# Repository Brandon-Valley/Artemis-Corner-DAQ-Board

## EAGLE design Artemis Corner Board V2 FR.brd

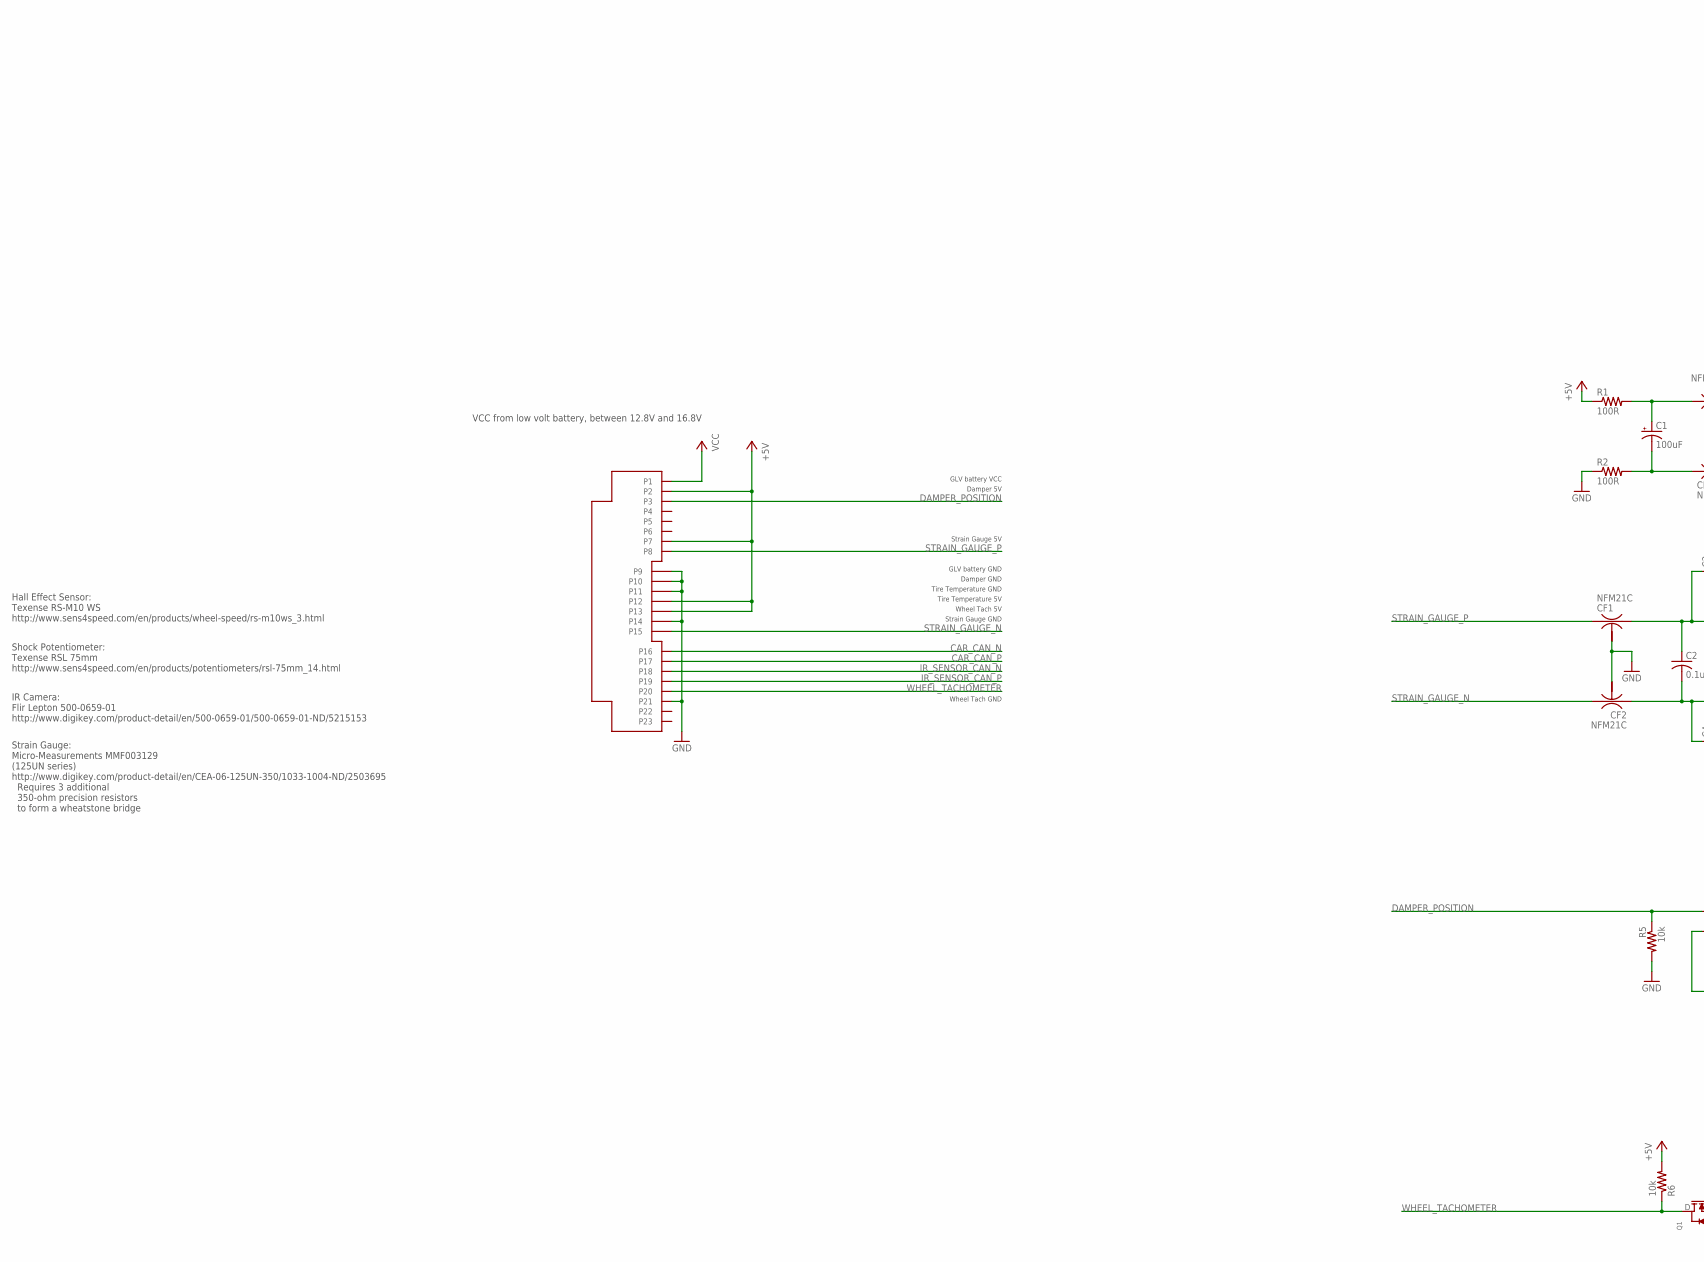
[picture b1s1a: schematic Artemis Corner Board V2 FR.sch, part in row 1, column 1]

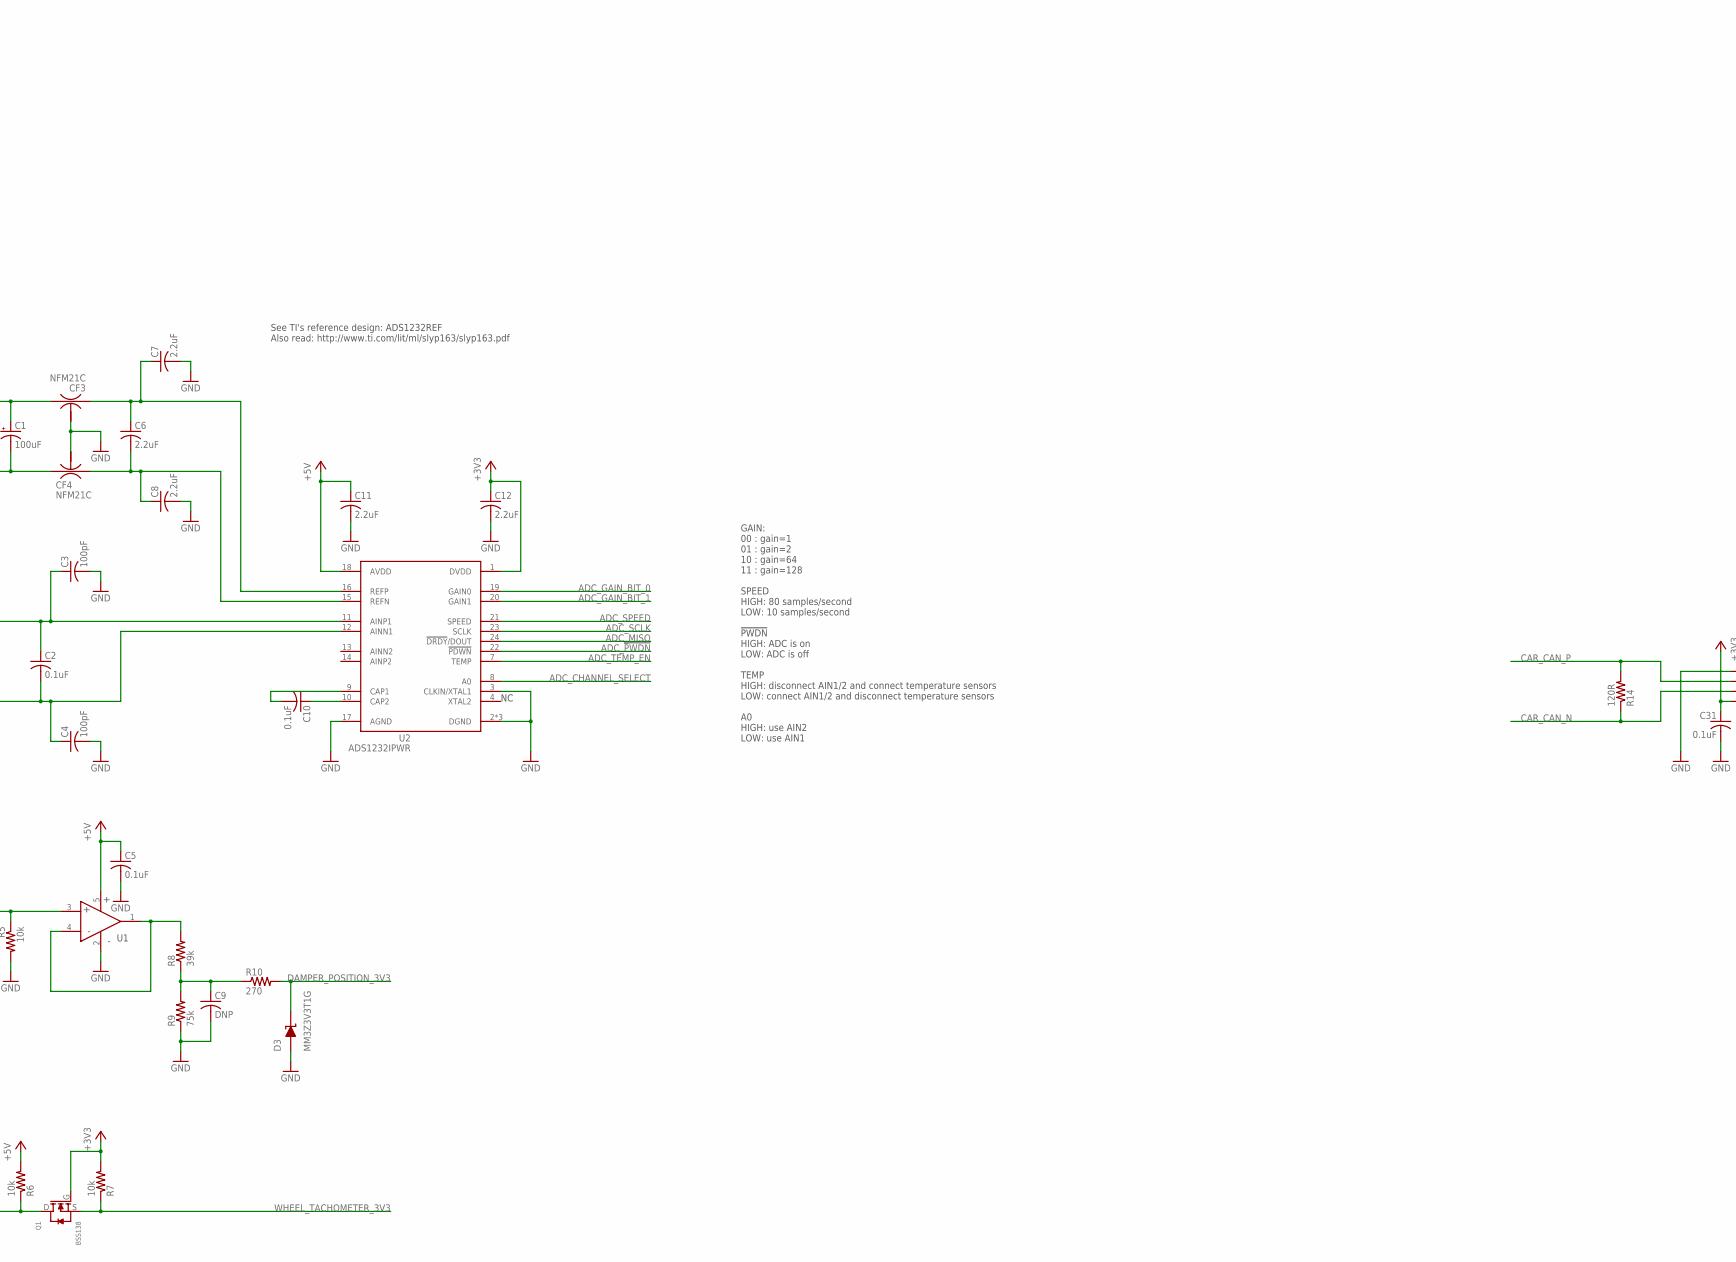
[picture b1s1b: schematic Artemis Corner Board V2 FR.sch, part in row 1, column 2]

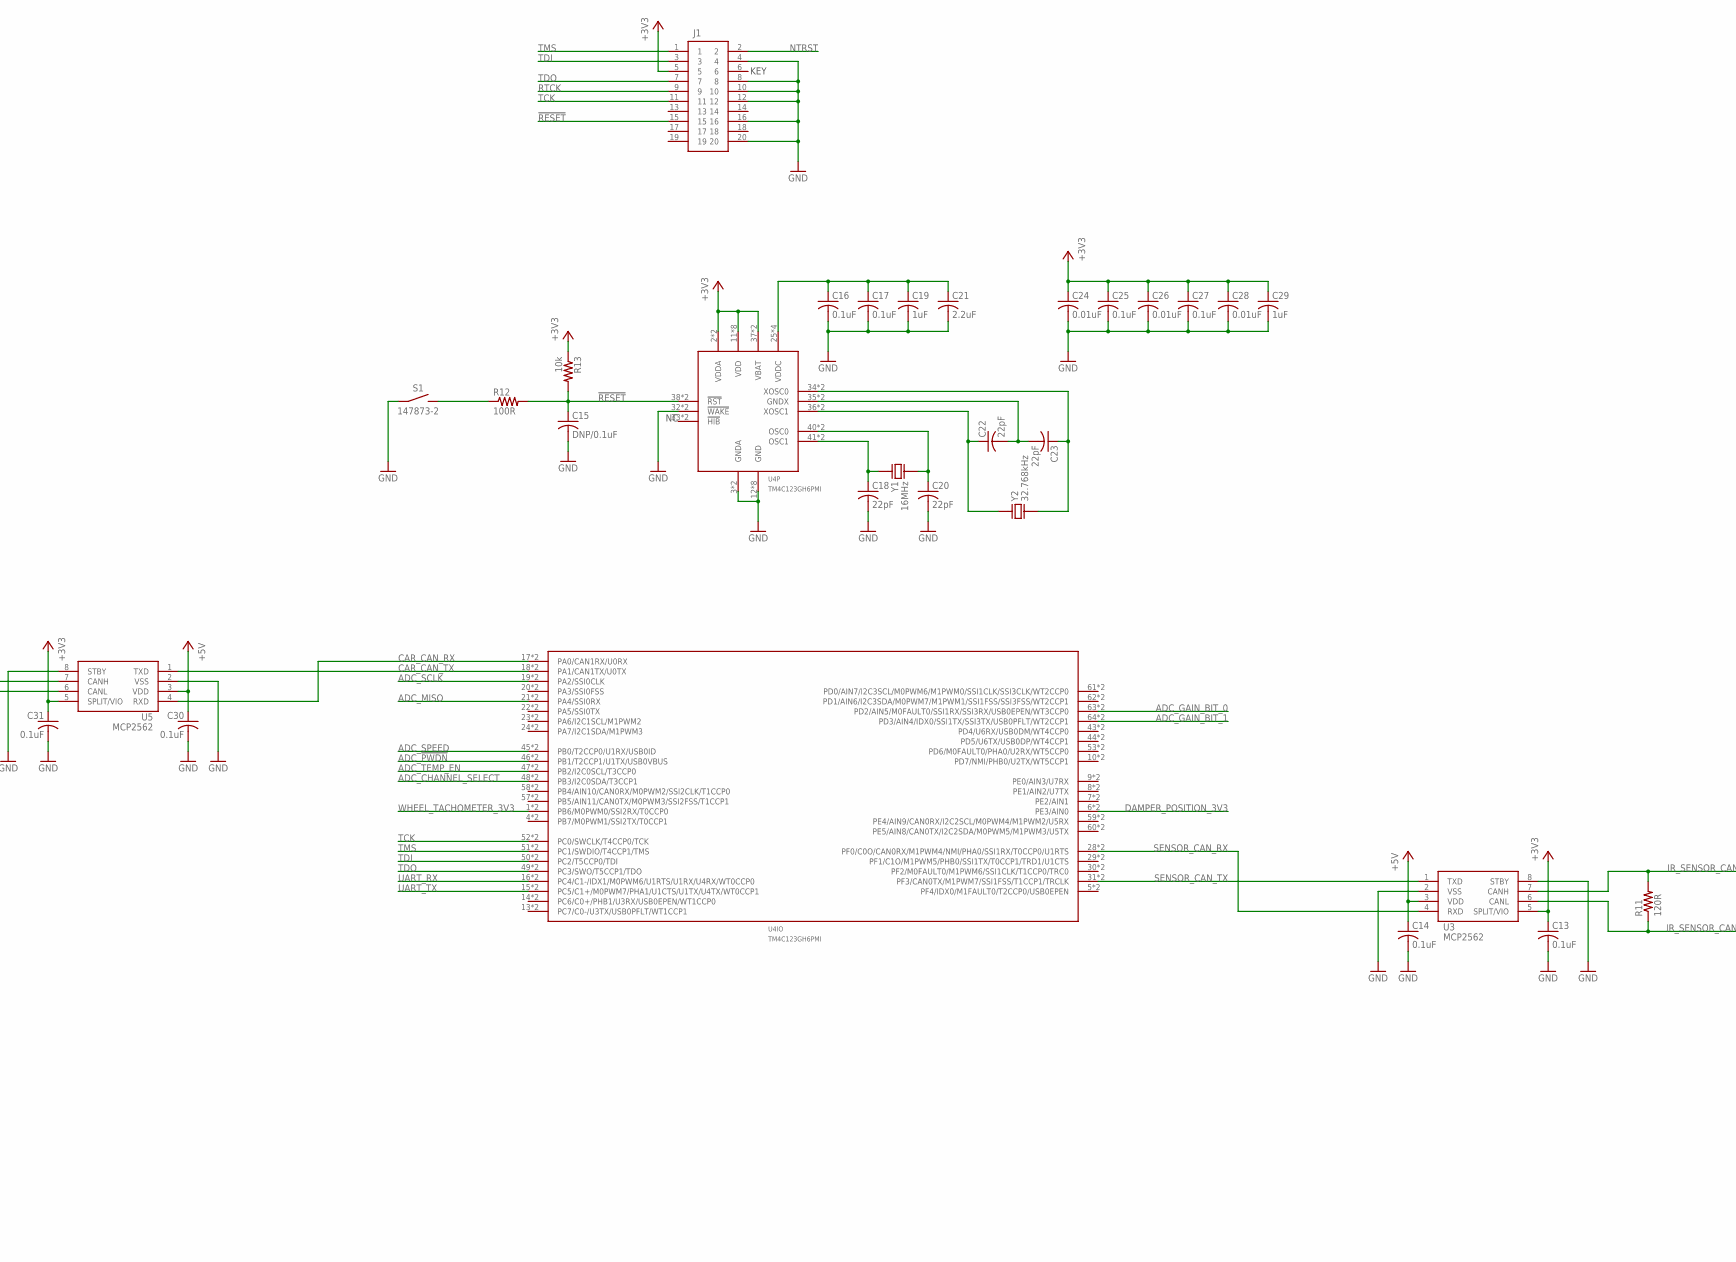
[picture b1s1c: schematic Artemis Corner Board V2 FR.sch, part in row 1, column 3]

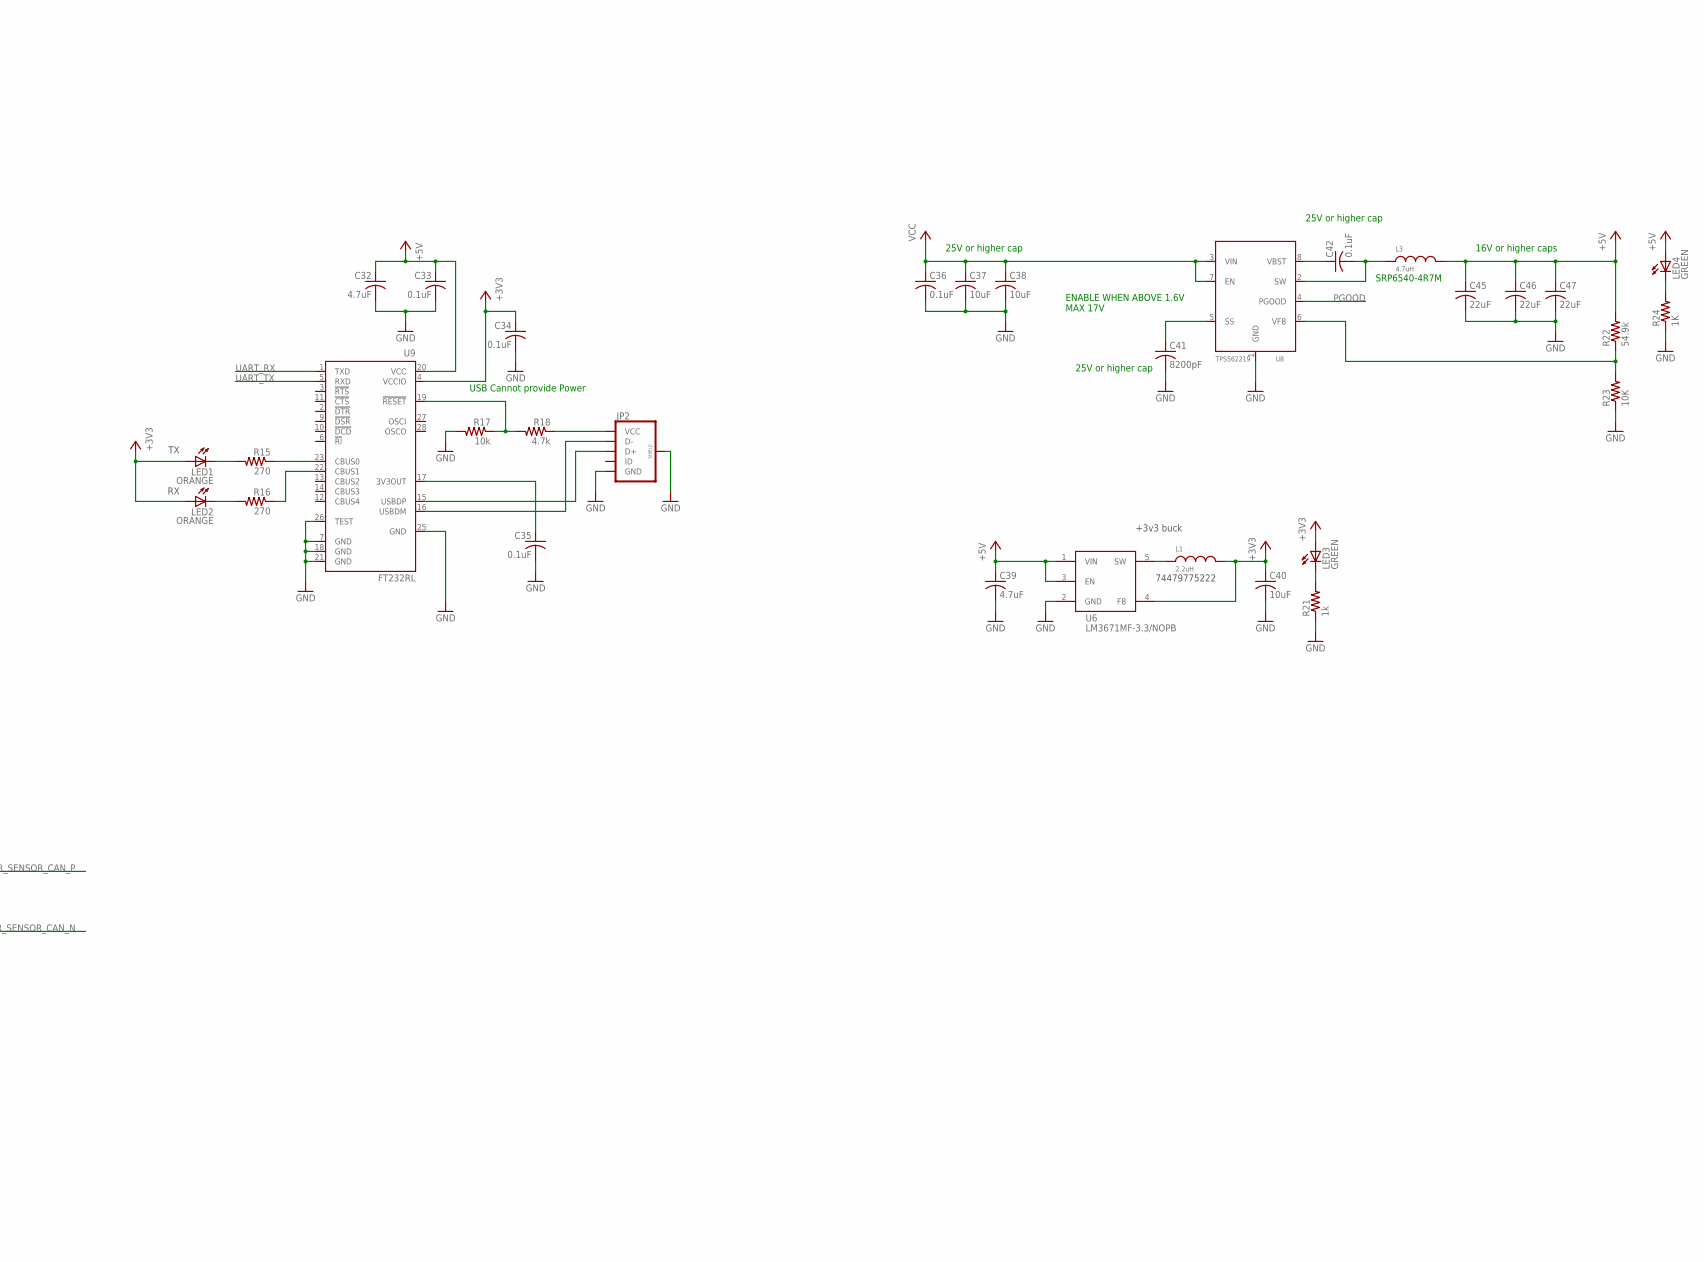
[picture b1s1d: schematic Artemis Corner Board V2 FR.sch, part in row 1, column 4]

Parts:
C1: 100uF; D/7343-31W; PARTNO T494D107K010AT
C2, C10: 0.1uF; C0805; PARTNO *
C3, C4: 100pF; C0805; PARTNO *
C5, C13, C14, C16, C17, C25, C27, C30, C31, C33, C34, C35, C36, C42: 0.1uF; C0805; PARTNO GRM21BR71E104KA01L
C6, C7, C8, C11, C12, C21: 2.2uF; C0805; PARTNO *
C9: DNP; C0805; PARTNO *
C15: DNP/0.1uF; C0805; PARTNO *
C18, C20, C22, C23: 22pF; C0805; PARTNO C0805C220K5GACTU
C19, C29: 1uF; C0805; PARTNO *
C24, C26, C28: 0.01uF; C0805; PARTNO *
C32: 4.7uF; C0805; PARTNO GRM21BR71A475KA73K
C37, C38: 10uF; C0805; PARTNO GRM21BR61E106KA73L
C39: 4.7uF; C0805
C40: 10uF; C0805
C41: 8200pF; C0805; PARTNO C0805C822K5RACTU
C45, C46, C47: 22uF; C0805; PARTNO C2012JB1E226M125AC
CF1, CF2, CF3, CF4: NFM21C; PARTNO NFM21PC105B1C3D
D3: MM3Z3V3T1G; SOD-323; PARTNO MM3Z3V3T1G
H1: 776228-4
J1: CTI-20-MALE; SAMTEC-FTR-DUALROW; PARTNO M50-3601042
JP2: USB_MICROB_PLUG-PTH3; MOLEX-MICROUSB-B-105017-0001; PARTNO 1050170001
L1: 2.2uH; 0805; PARTNO 74479775222
L3: 4.7uH; SRP6540; PARTNO SRP6540-4R7M
LED1, LED2: ORANGE; CHIP-LED0805; PARTNO 598-8130-107F
LED3, LED4: GREEN; CHIP-LED0805; PARTNO 598-8170-107F
Q1: BSS138
R1, R2: 100R; R0805
R5, R6, R7, R17: 10k; R0805; PARTNO ERJ-6ENF1002V
R8: 39k; R0805; PARTNO ERJ-6ENF3902V
R9: 75k; R0805; PARTNO ERJ-6ENF7502V
R10, R15, R16: 270; R0805; PARTNO ERJ-6ENF2700V
R11, R14: 120R; R0805; PARTNO ERJ-6ENF1200V
R12: 100R; R0805; PARTNO *
R13: 10k; R0805; PARTNO *
R18: 4.7k; R0805; PARTNO ERJ-6ENF4701V
R21: 1k; R0805; PARTNO ERJ-6ENF1001V
R22: 54.9k; R0805; PARTNO ERA-6AEB5492V
R23: 10K; R0805; PARTNO ERJ-6ENF1002V
R24: 1K; R0805; PARTNO ERJ-6ENF1001V
S1: 147873-2; TE-147873-2; PARTNO 147873-2
U1: OPA365AIDBVR; SOT23-5
U2: ADS1232IPWR; ADS1232IPW
U3, U5: MCP2562; SOIC8-N_MC; PARTNO MCP2562FD-E/SN
U4: TM4C123GH6PMI; PQFP-64
U6: LM3671MF-3.3/NOPB; SOT23-5
U8: TPS562219; PARTNO *
U9: FT232RL; SSOP28; PARTNO FT232RL-REEL
Y1: 16MHz; CSM-3X; PARTNO ECS-160-20-3X-TR
Y2: 32.768kHz; AB26TRQ; PARTNO AB26TRQ-32.768KHZ-T

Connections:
!RESET!: C15.1, J1.15, R12.2, R13.2, U4.38 (!RST!), U4.MASK-38 (!RST!)
+3V3: C12.1, C13.1, C24.1, C25.1, C26.1, C27.1, C28.1, C29.1, C31.1, C34.1, C40.1, J1.5, L1.2, LED1.A, LED2.A, LED3.A, Q1.G, R7.2, R13.1, U2.1 (DVDD), U3.5 (SPLIT/VIO), U4.2 (VDDA), U4.11 (VDD), U4.26 (VDD), U4.37 (VBAT), U4.42 (VDD), U4.54 (VDD), U4.MASK-2 (VDDA), U4.MASK-11 (VDD), U4.MASK-26 (VDD), U4.MASK-37 (VBAT), U4.MASK-42 (VDD), U4.MASK-54 (VDD), U5.5 (SPLIT/VIO), U6.4 (FB), U9.4 (VCCIO)
+5V: C5.1, C11.1, C14.1, C30.1, C32.1, C33.1, C39.1, C45.1, C46.1, C47.1, H1.P$2 (P2), H1.P$7 (P7), H1.P$12 (P12), H1.P$13 (P13), L3.P$2, LED4.A, R1.1, R6.2, R22.2, U1.5 (V+), U2.18 (AVDD), U3.3 (VDD), U5.3 (VDD), U6.1 (VIN), U6.3 (EN), U9.20 (VCC)
ADC_!PWDN!: U2.22 (!PDWN!), U4.46 (PB1/T2CCP1/U1TX/USB0VBUS), U4.MASK-46 (PB1/T2CCP1/U1TX/USB0VBUS)
ADC_CHANNEL_SELECT: U2.8 (A0), U4.48 (PB3/I2C0SDA/T3CCP1), U4.MASK-48 (PB3/I2C0SDA/T3CCP1)
ADC_GAIN_BIT_0: U2.19 (GAIN0), U4.63 (PD2/AIN5/M0FAULT0/SSI1RX/SSI3RX/USB0EPE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), U4.MASK-63 (PD2/AIN5/M0FAULT0/SSI1RX/SSI3RX/USB0EPE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)
ADC_GAIN_BIT_1: U2.20 (GAIN1), U4.64 (PD3/AIN4/IDX0/SSI1TX/SSI3TX/USB0PFLT/WT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), U4.MASK-64 (PD3/AIN4/IDX0/SSI1TX/SSI3TX/USB0PFLT/WT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)
ADC_MISO: U2.24 (!DRDY!/DOUT), U4.21 (PA4/SSI0RX), U4.MASK-21 (PA4/SSI0RX)
ADC_SCLK: U2.23 (SCLK), U4.19 (PA2/SSI0CLK), U4.MASK-19 (PA2/SSI0CLK)
ADC_SPEED: U2.21 (SPEED), U4.45 (PB0/T2CCP0/U1RX/USB0ID), U4.MASK-45 (PB0/T2CCP0/U1RX/USB0ID)
ADC_TEMP_EN: U2.7 (TEMP), U4.47 (PB2/I2C0SCL/T3CCP0), U4.MASK-47 (PB2/I2C0SCL/T3CCP0)
CAR_CAN_N: H1.P$16 (P16), R14.1, U5.6 (CANL)
CAR_CAN_P: H1.P$17 (P17), R14.2, U5.7 (CANH)
CAR_CAN_RX: U4.17 (PA0/CAN1RX/U0RX), U4.MASK-17 (PA0/CAN1RX/U0RX), U5.4 (RXD)
CAR_CAN_TX: U4.18 (PA1/CAN1TX/U0TX), U4.MASK-18 (PA1/CAN1TX/U0TX), U5.1 (TXD)
DAMPER_POSITION: H1.P$3 (P3), R5.1, U1.3 (NONINVERTING)
DAMPER_POSITION_3V3: D3.CATHODE, R10.2, U4.6 (PE3/AIN0), U4.MASK-6 (PE3/AIN0)
GND: C3.2, C4.2, C5.2, C7.2, C8.2, C9.2, C11.2, C12.2, C13.2, C14.2, C15.2, C16.2, C17.2, C18.2, C19.2, C20.2, C21.2, C24.2, C25.2, C26.2, C27.2, C28.2, C29.2, C30.2, C31.2, C32.2, C33.2, C34.2, C35.2, C36.2, C37.2, C38.2, C39.2, C40.2, C41.2, C45.2, C46.2, C47.2, CF1.2@1 (2), CF2.2@1 (2), CF3.2@1 (2), CF4.2@1 (2), D3.ANODE, H1.P$9 (P9), H1.P$10 (P10), H1.P$11 (P11), H1.P$14 (P14), H1.P$21 (P21), J1.4, J1.8, J1.10, J1.12, J1.16, J1.20, JP2.5 (GND), JP2.P$5 (GND), JP2.P$6 (SHIELD), JP2.P$7 (SHIELD), JP2.P$8 (SHIELD), JP2.P$9 (SHIELD), R2.1, R5.2, R9.1, R17.2, R21.1, R23.1, R24.1, S1.P$1 (1), U1.2 (V-), U2.2 (DGND), U2.3 (CLKIN/XTAL1), U2.5 (DGND), U2.6 (DGND), U2.17 (AGND), U3.2 (VSS), U3.8 (STBY), U4.3 (GNDA), U4.12 (GND), U4.27 (GND), U4.32 (!WAKE!), U4.39 (GND), U4.55 (GND), U4.MASK-3 (GNDA), U4.MASK-12 (GND), U4.MASK-27 (GND), U4.MASK-32 (!WAKE!), U4.MASK-39 (GND), U4.MASK-55 (GND), U5.2 (VSS), U5.8 (STBY), U6.2 (GND), U8.1 (GND), U9.7 (GND), U9.18 (GND), U9.21 (GND), U9.25 (GND), U9.26 (TEST)
IR_SENSOR_CAN_N: H1.P$18 (P18), R11.1, U3.6 (CANL)
IR_SENSOR_CAN_P: H1.P$19 (P19), R11.2, U3.7 (CANH)
unnamed: C18.1, U4.41 (OSC1), U4.MASK-41 (OSC1), Y1.P$1
unnamed: LED3.C, R21.2
unnamed: LED4.C, R24.2
unnamed: C20.1, U4.40 (OSC0), U4.MASK-40 (OSC0), Y1.P$2
unnamed: C10.1, U2.10 (CAP2)
unnamed: R12.1, S1.P$2 (2)
unnamed: C10.2, U2.9 (CAP1)
unnamed: C6.1, C7.1, CF3.1, U2.16 (REFP)
unnamed: L1.1, U6.5 (SW)
unnamed: C6.2, C8.1, CF4.3, U2.15 (REFN)
unnamed: C1.+, CF3.3, R1.2
unnamed: R8.2, U1.1 (OUT), U1.4 (INVERTING)
unnamed: C22.1, U4.36 (XOSC1), U4.MASK-36 (XOSC1), Y2.1
unnamed: C9.1, R8.1, R9.2, R10.1
unnamed: C23.1, U4.34 (XOSC0), U4.MASK-34 (XOSC0), Y2.2
unnamed: C1.-, CF4.1, R2.2
unnamed: C35.1, U9.17 (3V3OUT)
unnamed: JP2.1 (VCC), JP2.P$1 (VCC), R18.1
unnamed: C22.2, C23.2, U4.35 (GNDX), U4.MASK-35 (GNDX)
unnamed: C2.1, C3.1, CF1.3, U2.11 (AINP1)
unnamed: C2.2, C4.1, CF2.1, U2.12 (AINN1)
unnamed: R16.1, U9.22 (CBUS1)
unnamed: R15.1, U9.23 (CBUS0)
unnamed: LED1.C, R15.2
unnamed: LED2.C, R16.2
unnamed: R17.1, R18.2, U9.19 (!RESET)
NTRST: J1.2
PGOOD: U8.4 (PGOOD)
RTCK: J1.9
SENSOR_CAN_RX: U3.4 (RXD), U4.28 (PF0/C0O/CAN0RX/M1PWM4/NMI/PHA0/SSI1RX/T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), U4.MASK-28 (PF0/C0O/CAN0RX/M1PWM4/NMI/PHA0/SSI1RX/T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)
SENSOR_CAN_TX: U3.1 (TXD), U4.31 (PF3/CAN0TX/M1PWM7/SSI1FSS/T1CCP1/TRCLK), U4.MASK-31 (PF3/CAN0TX/M1PWM7/SSI1FSS/T1CCP1/TRCLK)
SS_5V: C41.1, U8.5 (SS)
STRAIN_GAUGE_N: CF2.3, H1.P$15 (P15)
STRAIN_GAUGE_P: CF1.1, H1.P$8 (P8)
SW_5V: C42.2, L3.P$1, U8.2 (SW)
TCK: J1.11, U4.52 (PC0/SWCLK/T4CCP0/TCK), U4.MASK-52 (PC0/SWCLK/T4CCP0/TCK)
TDI: J1.3, U4.50 (PC2/T5CCP0/TDI), U4.MASK-50 (PC2/T5CCP0/TDI)
TDO: J1.7, U4.49 (PC3/SWO/T5CCP1/TDO), U4.MASK-49 (PC3/SWO/T5CCP1/TDO)
TMS: J1.1, U4.51 (PC1/SWDIO/T4CCP1/TMS), U4.MASK-51 (PC1/SWDIO/T4CCP1/TMS)
UART_RX: U4.16 (PC4/C1-/IDX1/M0PWM6/U1RTS/U1RX/U4RX/WT0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), U4.MASK-16 (PC4/C1-/IDX1/M0PWM6/U1RTS/U1RX/U4RX/WT0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), U9.1 (TXD)
UART_TX: U4.15 (PC5/C1+/M0PWM7/PHA1/U1CTS/U1TX/U4TX/WT0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), U4.MASK-15 (PC5/C1+/M0PWM7/PHA1/U1CTS/U1TX/U4TX/WT0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), U9.5 (RXD)
USB_D_N: JP2.2 (D-), JP2.P$2 (D-), U9.16 (USBDM)
USB_D_P: JP2.3 (D+), JP2.P$3 (D+), U9.15 (USBDP)
VBST_5V: C42.1, U8.8 (VBST)
VCC: C36.1, C37.1, C38.1, H1.P$1 (P1), U8.3 (VIN), U8.7 (EN)
VDDC: C16.1, C17.1, C19.1, C21.1, U4.25 (VDDC), U4.56 (VDDC), U4.MASK-25 (VDDC), U4.MASK-56 (VDDC)
VFB_5V: R22.1, R23.2, U8.6 (VFB)
WHEEL_TACHOMETER: H1.P$20 (P20), Q1.D, R6.1
WHEEL_TACHOMETER_3V3: Q1.S, R7.1, U4.1 (PB6/M0PWM0/SSI2RX/T0CCP0), U4.MASK-1 (PB6/M0PWM0/SSI2RX/T0CCP0)

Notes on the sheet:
VCC from low volt battery, between 12.8V and 16.8V
+3v3 buck
USB Cannot provide Power
KEY
SRP6540-4R7M
ENABLE WHEN ABOVE 1.6V MAX 17V
25V or higher cap
16V or higher caps
Strain Gauge GND
Damper GND
Wheel Tach GND
Tire Temperature GND
Tire Temperature 5V
Wheel Tach 5V
Damper 5V
Strain Gauge 5V
See TI's reference design: ADS1232REF Also read: http://www.ti.com/lit/ml/slyp163/slyp163.pdf
GAIN: 00 : gain=1 01 : gain=2 10 : gain=64 11 : gain=128 SPEED HIGH: 80 samples/second LOW: 10 samples/second !PWDN! HIGH: ADC is on LOW: ADC is off TEMP HIGH: disconnect AIN1/2 and connect temperature sensors LOW: connect AIN1/2 and disconnect temperature sensors A0 HIGH: use AIN2 LOW: use AIN1
Hall Effect Sensor: Texense RS-M10 WS http://www.sens4speed.com/en/products/wheel-speed/rs-m10ws_3.html
Shock Potentiometer: Texense RSL 75mm http://www.sens4speed.com/en/products/potentiometers/rsl-75mm_14.html
IR Camera: Flir Lepton 500-0659-01 http://www.digikey.com/product-detail/en/500-0659-01/500-0659-01-ND/5215153
Strain Gauge: Micro-Measurements MMF003129 (125UN series) http://www.digikey.com/product-detail/en/CEA-06-125UN-350/1033-1004-ND/2503695 Requires 3 additional 350-ohm precision resistors to form a wheatstone bridge
GLV battery VCC
GLV battery GND
74479775222

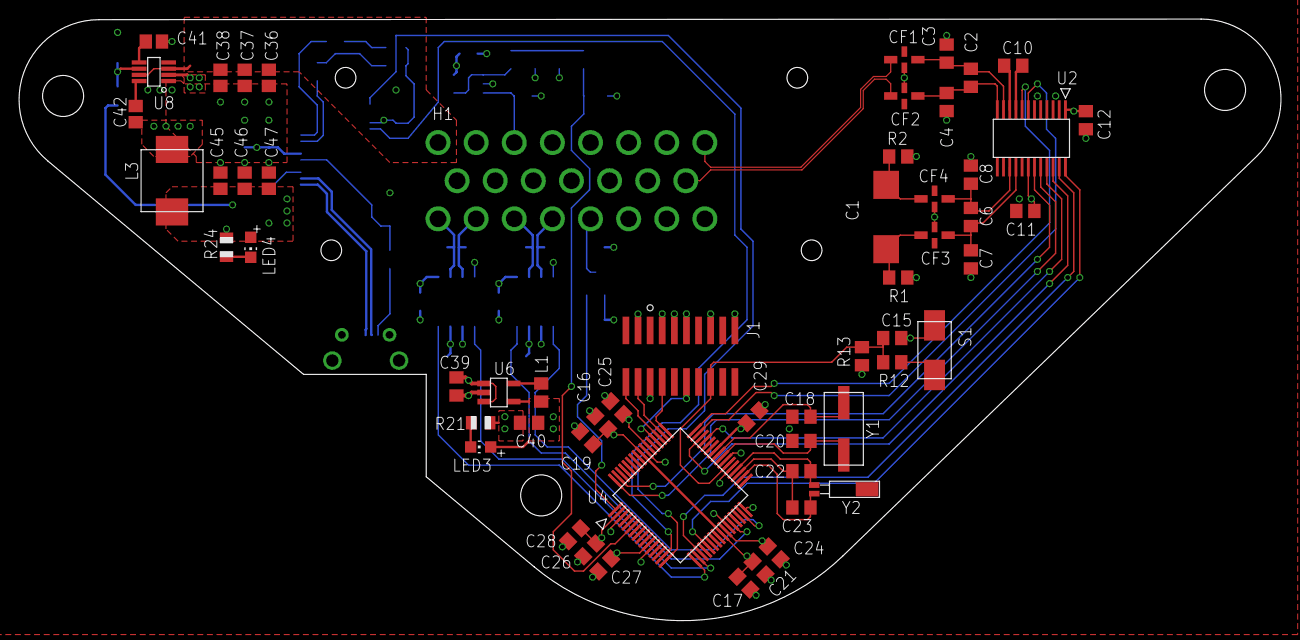
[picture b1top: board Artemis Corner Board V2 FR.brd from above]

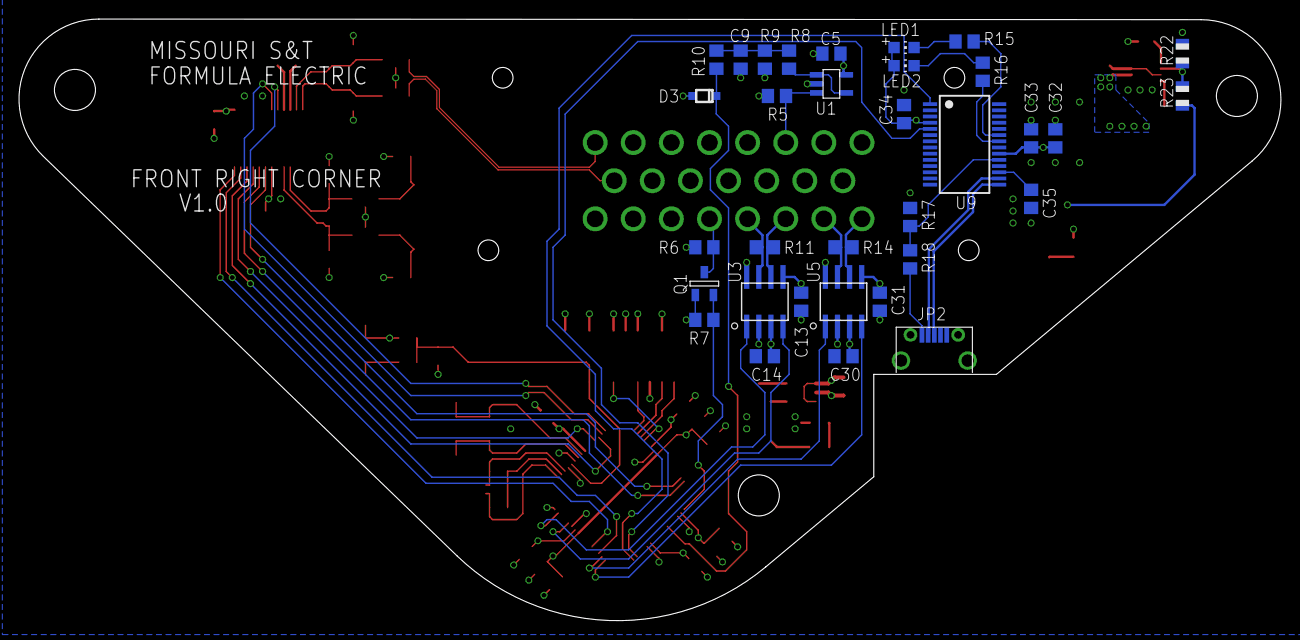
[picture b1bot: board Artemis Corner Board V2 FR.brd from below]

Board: 4 copper layers, 132.4 x 63.1 mm, 91 parts (33 on the bottom side), 66 nets.

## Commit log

2016-01-14 First Commit: At this point same as FL Corner Board
2016-01-14 Finally got shape right
2016-01-15 All regulators done, pin out for sealed connector almost done, need outs for image sensor
2016-01-16 About to delete 1V2 and 2V8 Regulators because switching Image sensor
2016-01-17 Everything done exept for scary LEDs
2016-01-19 Done (1st)
2016-01-20 Down to only 4 LEDs
2016-01-26 Added decoupling CAPS and Button for reset
2016-01-28 About to go from IR sensors to Image sensor
2016-01-30 Added Series Termination Resistors
2016-02-06 fixed board errors and added ESD Protection
2016-02-24 Made list fixes
2016-03-15 Updated a lot of stuff
2016-04-01 Changed to Tiva C with two CAN modules; modified sensor input scaling
2016-04-01 Grouped components in layout
2016-04-01 Changed to smaller LM3671 regulators
2016-04-01 Playing with layout arrangement
2016-04-01 Switched to 23-pin ampseal connector
2016-04-02 Routed everything except the usb components, which may get removed.
2016-04-02 Crammed the usb circuitry onto the board
2016-04-02 Fixed dimension layer around usb port
2016-04-02 Moved reference designators
2016-04-02 Placed board labels/logo
2016-04-02 ERC/DRC fixes. This still needs to be mechanically reviewed
2016-04-18 Update gitignore
2016-04-18 Fixed layout of 5v regulator
2016-09-21 Added a few notes, about to start on new Corner DAQ Board
